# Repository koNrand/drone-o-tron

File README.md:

# *Drone o Tron* ->[Veröffentlichung/Publication](https://www.instagram.com/p/Cwxmp4OM5u2/?img_index=1)<-

Für Neulinge: Lade dieses Repository herunter, um die Dateien zu benutzen. Ein Öffnen über den Browser funktioniert in der Regel nicht! Klicke dazu auf den grünen Button 'Code' und dann auf 'Download ZIP'.

For newbies: Download this repository to use the files. Opening them via the browser usually does not work! Click on the green button 'Code' and then on 'Download ZIP'.

----------

english below

## DE:

Der ***Drone o Tron*** (DoT) ist einstimmiger Minisynthesizer mit Ribbonklaviatur, welche über ein Monoaudiokabel gesteuert wird. Inspiration hierfür sind der [Monotron]((https://www.korg.com/de/products/dj/monotron/index.php)) von Korg oder die [Pocket Operator](https://teenage.engineering/products/po) von Teenage Engineering. Der Synthesizer soll auf eine einzige, handliche Platine passen und mit zwei AAA-Batterien betrieben werden. Außerdem soll es einige einstellbare Effekte und Filter geben, über welche der Sound verändert werden kann.

In den Pre-Versionen bestehen aus der Simulation in [LTSpice](https://www.analog.com/en/design-center/design-tools-and-calculators/ltspice-simulator.html) und dem Testaufbau auf dem Steckbrett. Wer Interesse am kompletten Prozess des Projektes hat, oder Erklärungen zu den Teilschaltungen sucht, kann im `.archive`-Ordner vorbeischauen. Ich habe dort in den `README.md` die entsprechenden Infos und auch Erklärvideos zu den groben Grundlagen verlinkt. 

Als finalen Schritt im Projektmanagement und erste Hauptversion nach Simulation und Steckbrettaufbau habe ich nun  den Drone o Tron in [KiCad](kicad.org/) Schaltplaneditor und anschließend im Boardeditor aufgebaut. Ich habe auch hier nochmal einige Änderungen vorgenommen, neue Funktionen hinzugefügt und diese in einem selbst illustrierten Platinenlayout zusammenkommen lassen.

Eine Auflistung aller Änderungen findet sich in der `CHANGELOG.md`.

Die voll funktionsfähige Platine lässt sich für den eigenen Gebrauch mithilfe der `gerberfiles_v_1_0_rev1`-Ordner bestellen. EInfach die geünschte Version und dann bei PCB-Produzenten wie JLCPCB bestellen. Eine interaktive Aufbauhilfe (`interactive_assembly_list.html`) in Form einer .html Datei ist auch vorhanden, sodass die benötigen Bauteile auch keine Hürde darstellen.
Mögliche Händler hier sind LCSC, (zugehörig zu JLCPCB, einfachste Lösung) Mouser, Reichelt, TME, uvm.

### Außer dem KiCadprojekt sind enthalten:
- einige gerenderte Aufnahmen aus der 3D-Ansicht von KiCad, welche alle 3D-Bauteilmodelle, die Illustrationen und meien favorisierte Farbe für den Lötstoplack (lila) enthalten.
- S/W Vektorgrafikaufnahmen des Boards, welceh mithilfe des Board2Pdf-Plugins erstellt wurden
- eine BOM-Tabelle (Bill of Material) aller benötigter Bauteile
- eine aussführliche Bescheibung der Berechnungen, die ich für den Spannungsteiler der Klaviatur vorgenommen habe, sodass der NE555 als wohltemperierter VCO für tonale Musik verwendet werden kann

## Disclaimer
Mit jegllicher Änderung am Schaltplan oder dem Boarddesign erlischt 
die Nutzungserlaubnis der Board-Artworks, meines Logos sowie der Verwendung meiner
Referenzen. Eine Nennung des Originalurhebers ist jedoch unbedingt erwünscht
und entsprechend zu kennzeichnen. Eine Veröffentlichung der veränderten Schaltung muss unter derselben Creative Commons Lizens CC BY-NC-SA erfolgen. Die 
kommerzielle Nutzung ist ausgeschlossen. Alles frei nach dem Motto: Fair use only! ;-)

Mehr Informationen unter: https://creativecommons.org

Open hardware FTW <3

-------

## EN:
The ***Drone o Tron*** (DoT) is monophonic mini synthesizer with ribbon keyboard, which is controlled by a mono audio cable. Inspiration for this is the [Monotron]((https://www.korg.com/de/products/dj/monotron/index.php)) by Korg or the [Pocket Operator](https://teenage.engineering/products/po) by Teenage Engineering. The synthesizer is supposed to fit on a single, handy circuit board and run on two AAA batteries. There are also supposed to be some adjustable effects and filters through which the sound can be changed.

In the pre-versions consist of the simulation in [LTSpice](https://www.analog.com/en/design-center/design-tools-and-calculators/ltspice-simulator.html) and the test setup on the breadboard. If you are interested in the complete process of the project, or if you are looking for explanations of the subcircuits, you can have a look in the `.archive` folder. I have linked there in the `README.md` the corresponding info and also explanatory videos to the rough basics. 

As a final step in the project management and first main version after simulation and board assembly I have now built the Drone o Tron in [KiCad](kicad.org/) schematic editor and afterwards in the board editor. Again, I made some changes, added new features and let them come together in a self-illustrated board layout.

A list of all changes can be found in the `CHANGELOG.md`.

The fully functional board can be found for your own use with the help of the `.gerberfiles_v_1_0_rev0` folder. Choose your favorite version and zip it. The board can then be ordered from PCB producers like JLCPCB. An interactive assembly help (`interactive_assembly_list.html`) in form of a .html file is also available, so that the needed components are no hurdle. Possible distributors here are LCSC, (belonging to JLCPCB, simpliest solution) Mouser, Reichelt, TME, and many more.

### Besides the KiCad project, included are:
- some rendered shots from the 3D view of KiCad, containing all 3D component models, the illustrations and my favorite color for the solder mask (purple).
- B/W vector graphic images of the board, which were created using the Board2Pdf plugin
- a BOM table (Bill of Material) of all needed components
- a detailed description of the calculations I did for the keyboard voltage divider, so that the NE555 can be used as a well-tempered VCO for tonal music

## Disclaimer
With any change to the schematic or the board design the usage permission of the 
the permission to use the board artwork, my logo and the use of my references.
references. A naming of the original author is however absolutely desired
and must be marked accordingly. A publication of the modified circuit must be made under the same Creative Commons license CC BY-NC-SA. The 
commercial use is excluded. Everything freely after the slogan: Fair use only! ;-)

More information at: https://creativecommons.org

Open hardware FTW <33

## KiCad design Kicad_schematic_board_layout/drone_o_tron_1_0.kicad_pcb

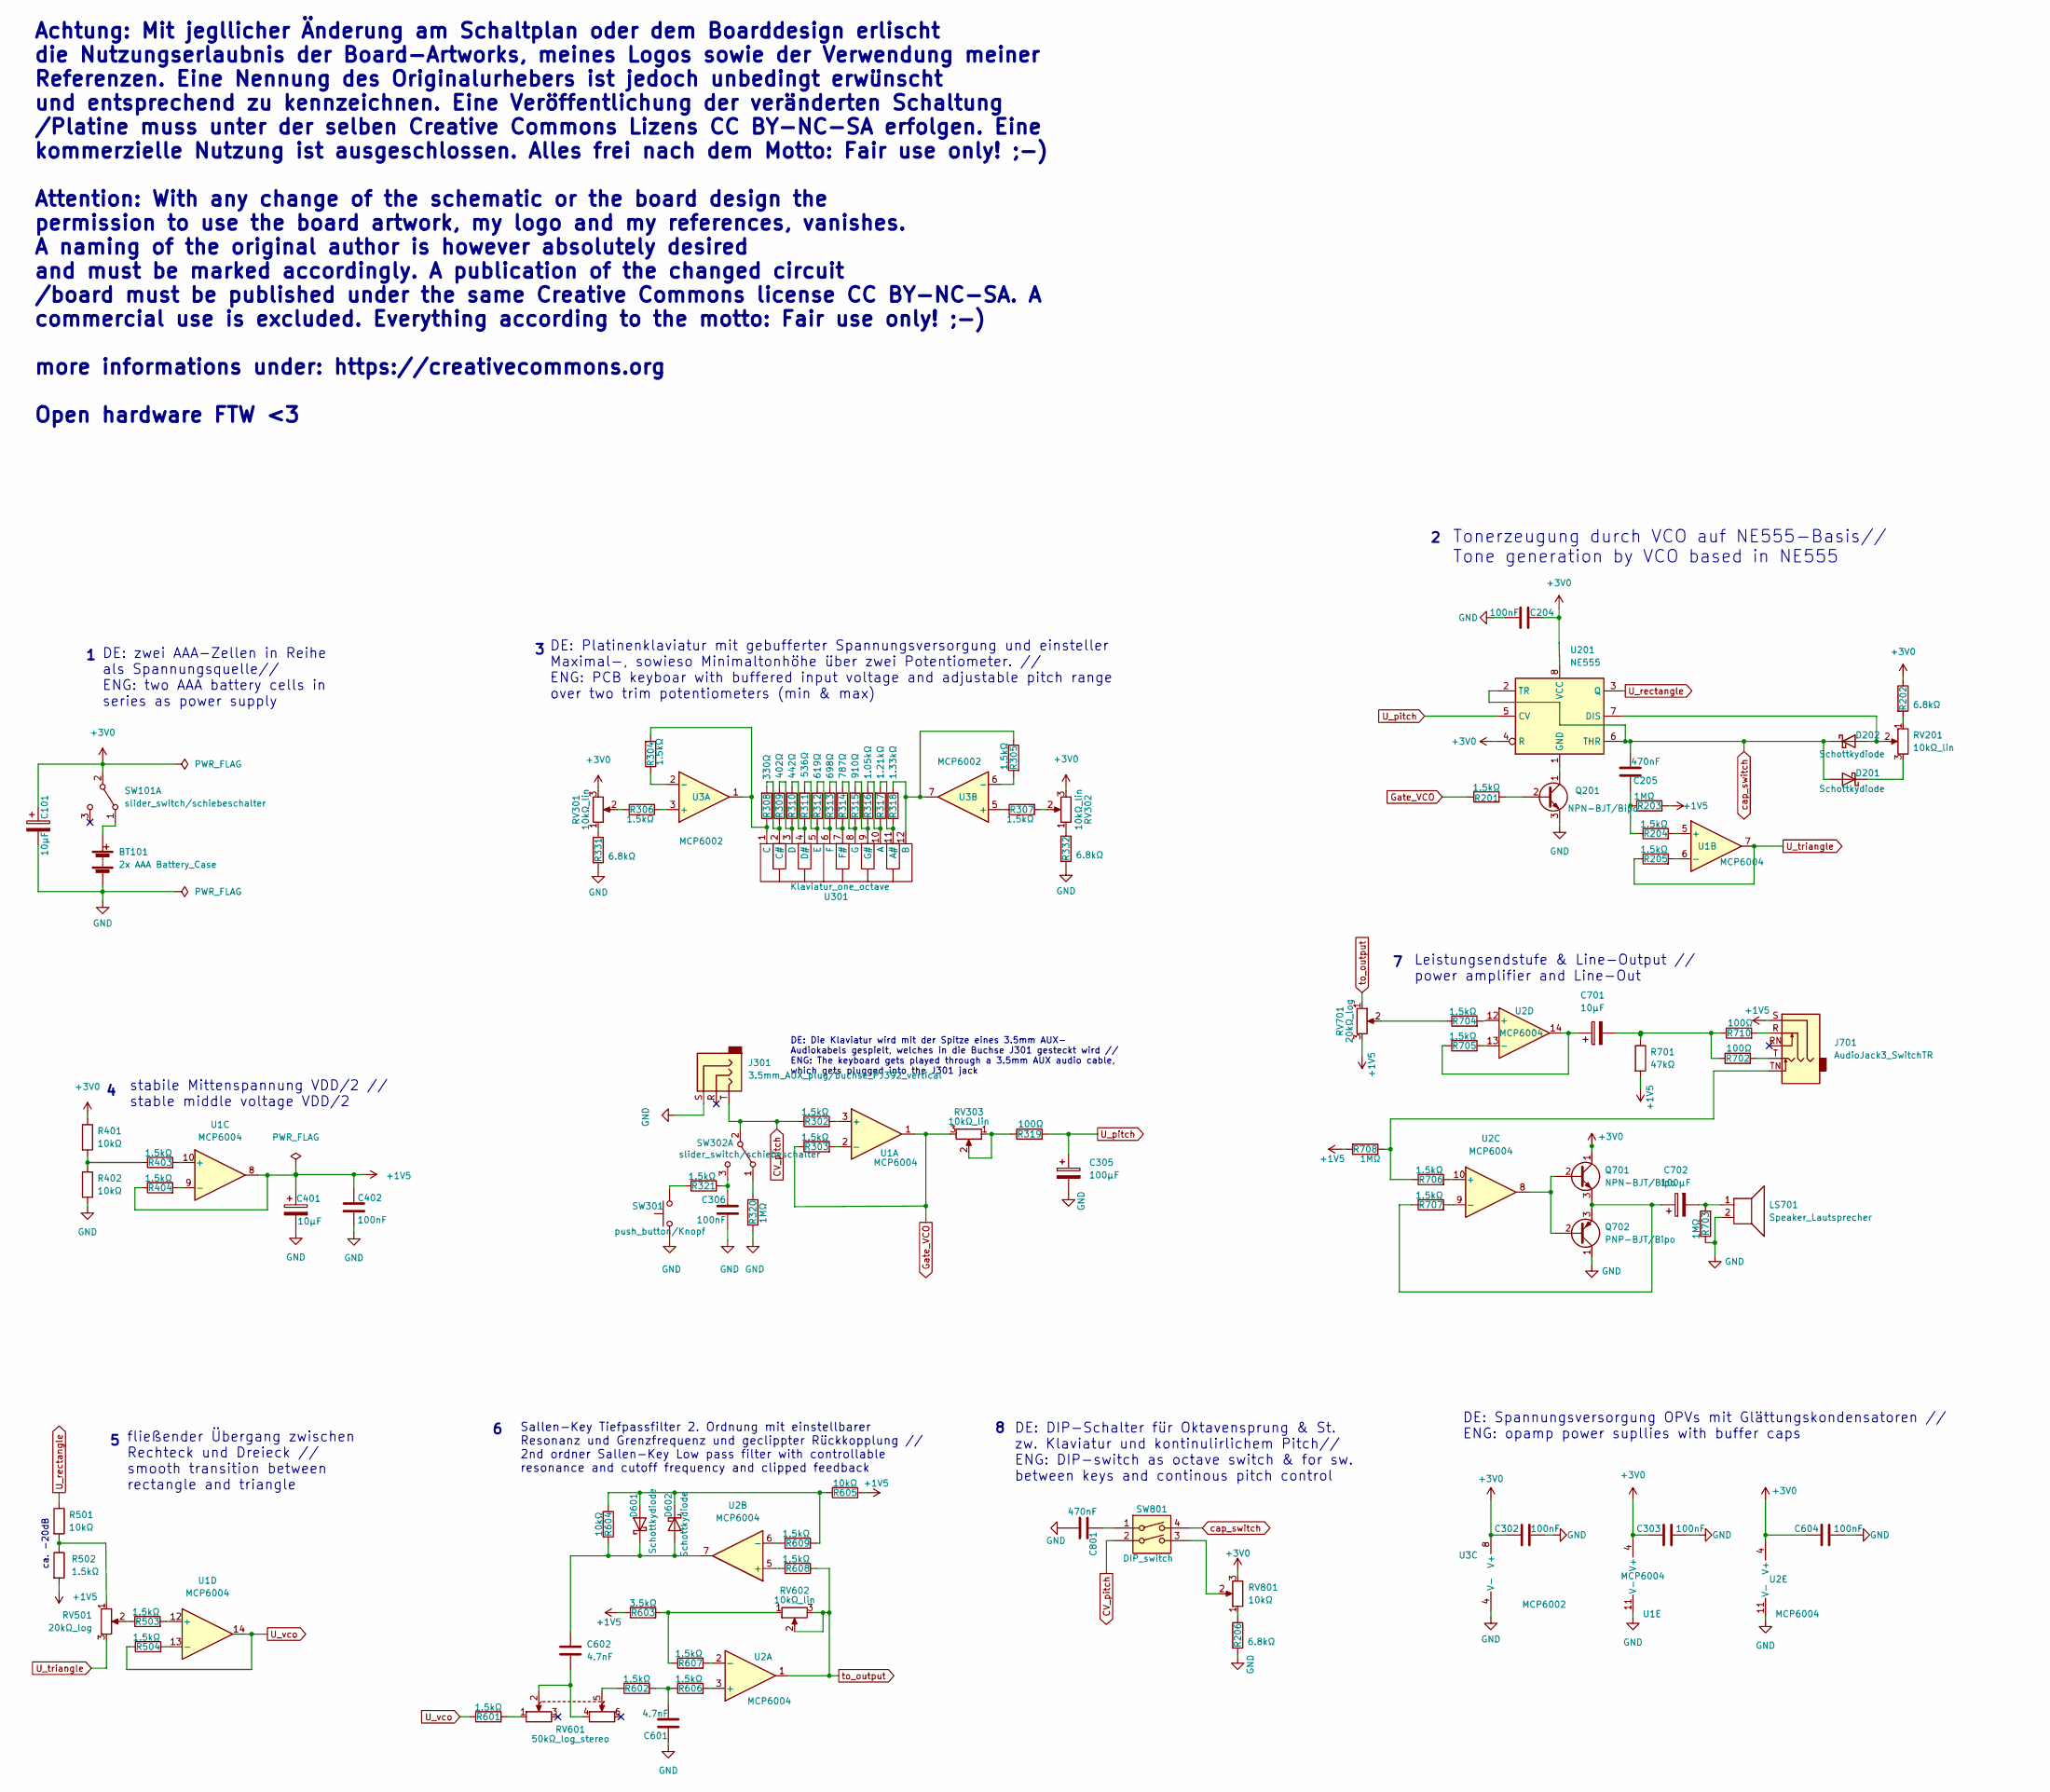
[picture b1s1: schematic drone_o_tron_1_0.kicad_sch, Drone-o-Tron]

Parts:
BT101: 2x AAA Battery_Case; Reichelt_Batteriehalter_2_AAA
C101, C401, C701: 10µF; C_Disc_D6.0mm_W4.4mm_P5.00mm
C204, C302, C303, C306, C402, C604: 100nF; C_Disc_D5.0mm_W2.5mm_P5.00mm
C205, C801: 470nF; C_Disc_D6.0mm_W4.4mm_P5.00mm
C305, C702: 100µF; CP_Radial_D5.0mm_P2.50mm
C601, C602: 4.7nF; C_Disc_D3.8mm_W2.6mm_P2.50mm
D201, D202, D601, D602: Schottkydiode; D_DO-35_SOD27_P7.62mm_Horizontal
J301: 3.5mm_AUX_plug/buchse_PJ392_vertical; PJ-392
J701: AudioJack3_SwitchTR; Audio_Jack_stereo_tip_ring_switch_PJ-307
LS701: Speaker_Lautsprecher; speaker_LSM-45F
Q201, Q701: NPN-BJT/Bipo; TO-92
Q702: PNP-BJT/Bipo; TO-92
R201, R204, R205, R302, R303, R304, R305, R306, R307, R321, R403, R404, R502, R503, R504, R601, R602, R606, R607, R608, R609, R704, R705, R706, R707: 1.5kΩ; R_Axial_DIN0204_L3.6mm_D1.6mm_P7.62mm_Horizontal
R202, R206, R331, R332: 6.8kΩ; R_Axial_DIN0204_L3.6mm_D1.6mm_P7.62mm_Horizontal
R203, R320, R703, R708: 1MΩ; R_Axial_DIN0204_L3.6mm_D1.6mm_P7.62mm_Horizontal
R308: 330Ω; R_Axial_DIN0204_L3.6mm_D1.6mm_P7.62mm_Horizontal
R309: 402Ω; R_Axial_DIN0204_L3.6mm_D1.6mm_P7.62mm_Horizontal
R310: 442Ω; R_Axial_DIN0204_L3.6mm_D1.6mm_P7.62mm_Horizontal
R311: 536Ω; R_Axial_DIN0204_L3.6mm_D1.6mm_P7.62mm_Horizontal
R312: 619Ω; R_Axial_DIN0204_L3.6mm_D1.6mm_P7.62mm_Horizontal
R313: 698Ω; R_Axial_DIN0204_L3.6mm_D1.6mm_P7.62mm_Horizontal
R314: 787Ω; R_Axial_DIN0204_L3.6mm_D1.6mm_P7.62mm_Horizontal
R315: 910Ω; R_Axial_DIN0204_L3.6mm_D1.6mm_P7.62mm_Horizontal
R316: 1.05kΩ; R_Axial_DIN0204_L3.6mm_D1.6mm_P7.62mm_Horizontal
R317: 1.21kΩ; R_Axial_DIN0204_L3.6mm_D1.6mm_P7.62mm_Horizontal
R318: 1.33kΩ; R_Axial_DIN0204_L3.6mm_D1.6mm_P7.62mm_Horizontal
R319, R702, R710: 100Ω; R_Axial_DIN0204_L3.6mm_D1.6mm_P7.62mm_Horizontal
R401, R402, R501, R604, R605: 10kΩ; R_Axial_DIN0204_L3.6mm_D1.6mm_P7.62mm_Horizontal
R603: 3.5kΩ; R_Axial_DIN0204_L3.6mm_D1.6mm_P7.62mm_Horizontal
R701: 47kΩ; R_Axial_DIN0204_L3.6mm_D1.6mm_P7.62mm_Horizontal
RV201, RV301, RV302, RV303, RV602: 10kΩ_lin; Potentiometer_Alps_RK09K_Single_Vertical
RV501, RV701: 20kΩ_log; Potentiometer_Alps_RK09K_Single_Vertical
RV601: 50kΩ_log_stereo; rk_1212G_stereo_potentiometer
RV801: 10kΩ; Potentiometer_Alps_RK09K_Single_Vertical
SW101, SW302: slider_switch/schiebeschalter; SW_CuK_OS102011MA1QN1_SPDT_Angled
SW301: push_button/Knopf; push_button_8mm
SW801: DIP_switch; SW_DIP_SPSTx02_Piano_10.8x6.64mm_W7.62mm_P2.54mm
U1, U2: MCP6004; DIP-14_W7.62mm
U3: MCP6002; DIP-8_W7.62mm_Socket
U201: NE555; DIP-8_W7.62mm
U301: Klaviatur_one_octave; PCB_piano_keys_1_ocatve_100mm

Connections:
+1V5: C401.1, C402.1, J701.S, R203.2, R404.1, R502.2, R603.1, R605.1, R701.2, R708.2, RV701.3, U1.8
+3V0: C101.1, C204.2, C302.1, C303.1, C604.1, Q701.1 (C), R202.1, R401.1, RV301.3, RV302.3, RV801.3, SW101.2 (B), U1.4 (V+), U2.4 (V+), U3.8 (V+), U201.4 (R), U201.8 (VCC)
CV_pitch: J301.T, R302.1, SW302.2 (B), SW801.2
GND: BT101.2 (-), C101.2, C204.1, C302.2, C303.2, C305.2, C306.1, C401.2, C402.2, C601.2, C604.2, C801.2, J301.S, LS701.2, Q201.3 (E), Q702.1 (C), R206.2, R320.2, R331.2, R332.2, R402.2, R703.1, SW301.1 (A), SW301.2 (A), U1.11 (V-), U2.11 (V-), U3.4 (V-)
Gate_VCO: R201.1, R303.1, RV303.3, U1.1
unnamed: BT101.1 (+), SW101.1 (A)
unnamed: C205.1, R203.1, R204.1
unnamed: C306.2, R321.2, SW302.3 (C)
unnamed: C601.1, R602.2, R606.1
unnamed: C602.1, D601.1 (K), D602.2 (A), R604.2, U2.7
unnamed: C602.2, RV601.2, RV601.4
unnamed: C701.1, R705.1, U2.14
unnamed: C701.2, R701.1, R702.1, R710.1
unnamed: C702.1, Q701.3 (E), Q702.3 (E), R707.1
unnamed: C702.2, LS701.1, R703.2
unnamed: C801.1, SW801.1
unnamed: D201.1 (K), RV201.3
unnamed: D202.2 (A), RV201.2, U201.7 (DIS)
unnamed: D601.2 (A), D602.1 (K), R604.1, R605.2, R609.2
unnamed: J701.R, R710.2
unnamed: J701.T, R702.2
unnamed: J701.TN, R706.1, R708.1
unnamed: Q201.1 (C), U201.1 (GND)
unnamed: Q201.2 (B), R201.2
unnamed: Q701.2 (B), Q702.2 (B), U2.8
unnamed: R202.2, RV201.1
unnamed: R204.2, U1.5 (+)
unnamed: R205.2, U1.6 (-)
unnamed: R206.1, RV801.1
unnamed: R302.2, U1.3 (+)
unnamed: R303.2, U1.2 (-)
unnamed: R304.1, U3.2 (-)
unnamed: R304.2, R308.1, U3.1, U301.1 (C)
unnamed: R305.1, R318.2, U3.7, U301.12 (B)
unnamed: R305.2, U3.6 (-)
unnamed: R306.1, RV301.2
unnamed: R306.2, U3.3 (+)
unnamed: R307.1, U3.5 (+)
unnamed: R307.2, RV302.2
unnamed: R308.2, R309.1, U301.2 (C#)
unnamed: R309.2, R310.1, U301.3 (D)
unnamed: R310.2, R311.1, U301.4 (D#)
unnamed: R311.2, R312.1, U301.5 (E)
unnamed: R312.2, R313.1, U301.6 (F)
unnamed: R313.2, R314.1, U301.7 (F#)
unnamed: R314.2, R315.1, U301.8 (G)
unnamed: R315.2, R316.1, U301.9 (G#)
unnamed: R316.2, R317.1, U301.10 (A)
unnamed: R317.2, R318.1, U301.11 (A#)
unnamed: R319.1, RV303.1, RV303.2
unnamed: R320.1, SW302.1 (A)
unnamed: R321.1, SW301.3 (B), SW301.4 (B)
unnamed: R331.1, RV301.1
unnamed: R332.1, RV302.1
unnamed: R401.2, R402.1, R403.1
unnamed: R403.2, U1.10 (+)
unnamed: R404.2, U1.9 (-)
unnamed: R501.2, R502.1, RV501.1
unnamed: R503.1, RV501.2
unnamed: R503.2, U1.12 (+)
unnamed: R504.2, U1.13 (-)
unnamed: R601.2, RV601.1
unnamed: R602.1, RV601.5
unnamed: R603.2, R607.1, RV602.1
unnamed: R606.2, U2.3 (+)
unnamed: R607.2, U2.2 (-)
unnamed: R608.1, U2.5 (+)
unnamed: R609.1, U2.6 (-)
unnamed: R704.1, RV701.2
unnamed: R704.2, U2.12 (+)
unnamed: R705.2, U2.13 (-)
unnamed: R706.2, U2.10 (+)
unnamed: R707.2, U2.9 (-)
unnamed: RV801.2, SW801.3
U_pitch: C305.1, R319.2, U201.5 (CV)
U_rectangle: R501.1, U201.3 (Q)
U_triangle: R205.1, RV501.3, U1.7
U_vco: R504.1, R601.1, U1.14
cap_switch: C205.2, D201.2 (A), D202.1 (K), SW801.4, U201.2 (TR), U201.6 (THR)
to_output: R608.2, RV602.2, RV602.3, RV701.1, U2.1

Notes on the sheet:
ca. -20dB
DE: Platinenklaviatur mit gebufferter Spannungsversorgung und einsteller Maximal-, sowieso Minimaltonhöhe über zwei Potentiometer. // ENG: PCB keyboar with buffered input voltage and adjustable pitch range over two trim potentiometers (min & max)
DE: Spannungsversorgung OPVs mit Glättungskondensatoren // ENG: opamp power supllies with buffer caps
Tonerzeugung durch VCO auf NE555-Basis// Tone generation by VCO based in NE555
Sallen-Key Tiefpassfilter 2. Ordnung mit einstellbarer Resonanz und Grenzfrequenz und geclippter Rückkopplung // 2nd ordner Sallen-Key Low pass filter with controllable resonance and cutoff frequency and clipped feedback
fließender Übergang zwischen Rechteck und Dreieck // smooth transition between rectangle and triangle
stabile Mittenspannung VDD/2 // stable middle voltage VDD/2
DE: zwei AAA-Zellen in Reihe als Spannungsquelle// ENG: two AAA battery cells in series as power supply
DE: DIP-Schalter für Oktavensprung & St. zw. Klaviatur und kontinulirlichem Pitch// ENG: DIP-switch as octave switch & for sw. between keys and continous pitch control
Leistungsendstufe & Line-Output // power amplifier and Line-Out
Achtung: Mit jegllicher Änderung am Schaltplan oder dem Boarddesign erlischt die Nutzungserlaubnis der Board-Artworks, meines Logos sowie der Verwendung meiner Referenzen. Eine Nennung des Originalurhebers ist jedoch unbedingt erwünscht und entsprechend zu kennzeichnen. Eine Veröffentlichung der ve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
DE: Die Klaviatur wird mit der Spitze eines 3.5mm AUX- Audiokabels gespielt, welches in die Buchse J301 gesteckt wird // ENG: The keyboard gets played through a 3.5mm AUX audio cable, which gets plugged into the J301 jack

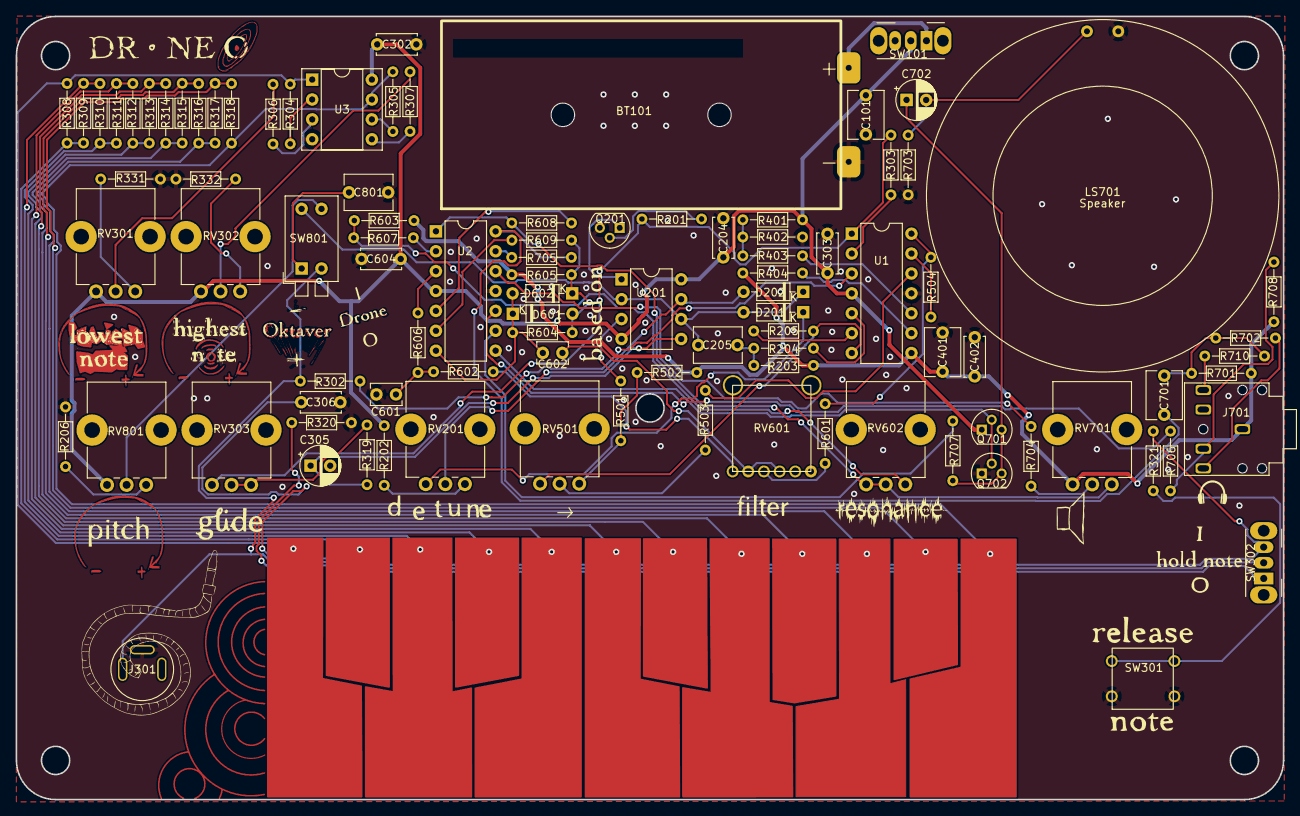
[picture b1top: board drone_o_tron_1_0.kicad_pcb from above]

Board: 2 copper layers, 161.8 x 100.0 mm, 98 parts (0 on the bottom side), 80 nets.

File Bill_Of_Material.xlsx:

Name | Value | amount
BT101 | 2x AAA Battery_Case | 1
> C204, C302, C303, C306, C402, C604 | 100nF | 6
> C601, C602 | 4.7nF | 2
> C101, C401, C701 | 10µF | 3
> C305, C702 | 100µF | 2
> C205, C801 | 470nF | 2
> D201, D202, D601, D602 | Schottkydiode | 4
J301 | 3.5mm_AUX_plug/buchse_PJ392_vertical | 1
J701 | AudioJack3_SwitchTR | 1
LS701 | Speaker_Lautsprecher | 1
> Q201, Q701 | NPN-BJT/Bipo | 2
Q702 | PNP-BJT/Bipo | 1
> R202, R206, R331, R332 | 6.8kΩ | 4
R308 | 330Ω | 1
R309 | 402Ω | 1
R310 | 442Ω | 1
R311 | 536Ω | 1
R312 | 619Ω | 1
R313 | 698Ω | 1
R314 | 787Ω | 1
R315 | 910Ω | 1
R316 | 1.05kΩ | 1
R317 | 1.21kΩ | 1
R318 | 1.33kΩ | 1
> R401, R402, R501, R604, R605 | 10kΩ | 5
> R201, R204, R205, R302-R307, R321, R403, R404, R502-R504, R601, R602, R606-R6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 | 1.5kΩ | 25
R603 | 3.5kΩ | 1
R701 | 47kΩ | 1
> R319, R702, R710 | 100Ω | 3
> R203, R320, R703, R708 | 1MΩ | 4
> RV501, RV701 | 20kΩ_log | 2
RV601 | 50kΩ_log_stereo | 1
> RV201, RV301-RV303, RV602 | 10kΩ_lin | 5
RV801 | 10kΩ | 1
> SW101, SW302 | slider_switch/schiebeschalter | 2
SW301 | push_button/Knopf | 1
SW801 | DIP_switch | 1
> U1, U2 | MCP6004 | 2
U3 | MCP6002 | 1
U201 | NE555 | 1
U301 | Klaviatur_one_octave | 1

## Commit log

2022-11-11 v.0.1 idea colloection and simulation
2022-11-11 v.0.2 - breadboard construction
2022-11-11 v.1.0.Rev0-Release
2022-11-11 v.1.0.Rev0-Release_of_Drone-o-Tron
2023-01-16 v.1.0Rev1
2026-01-30 Add publication link to README
    Updated README to include a link to the publication.
2026-01-30 Fix typo in publication link in README
2026-01-30 Fix typo in publication link text

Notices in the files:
Kicad_schematic_board_layout/drone_o_tron_1_0.kicad_pcb:
©Konrad Dirk Paul Panzer, 2022
lizensiert mit CC BY-NC-SA
Kicad_schematic_board_layout/drone_o_tron_1_0.kicad_sch:
Platine muss unter der selben Creative Commons Lizens CC BY-NC-SA erfolgen. Eine
board must be published under the same Creative Commons license CC BY-NC-SA. A
more informations under: https://creativecommons.org
